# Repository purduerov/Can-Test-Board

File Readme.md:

# Readme for Can-Test-Board

Whenever you make a new part, download the datasheet and save it here _**and**_ with the part in the parts library

Always pull other people's changes before beginning to work
`git pull`

Be sure to push your changes after  working on them. Run:
1. `git add .` to add any files in this directory or a subdirectory
or `git add -u` to add any modified files
2. (Optional) `git clean -nX` to see what ignored files can be removed
	`git clean -fX` removes ignored files (Eagle backups)
3. `git commit -m "helpful commit message"` with a description of the work that you did
4. `git push` to push your work to github

Other helpful commands
* `git status` says information about modified and staged files
* `git log` shows the recent commits of the repository
* `git log filename.extension` show the recent commits for just that file
* `git checkout first-couple-letter-of-commit-id` lets you go back to a previous version
* `git checkout master` brings you back to the latest commit
* `git tag` lists the tags
* `git tag -a orderX -m "the version of the board placed for the X'th order"` tag a specific commit
* `git push --tags` needed to push tags to remote
* `git show orderX` show the commit log for the given tag
* `git checkout orderX` go back and interact with the files at the tagged commit

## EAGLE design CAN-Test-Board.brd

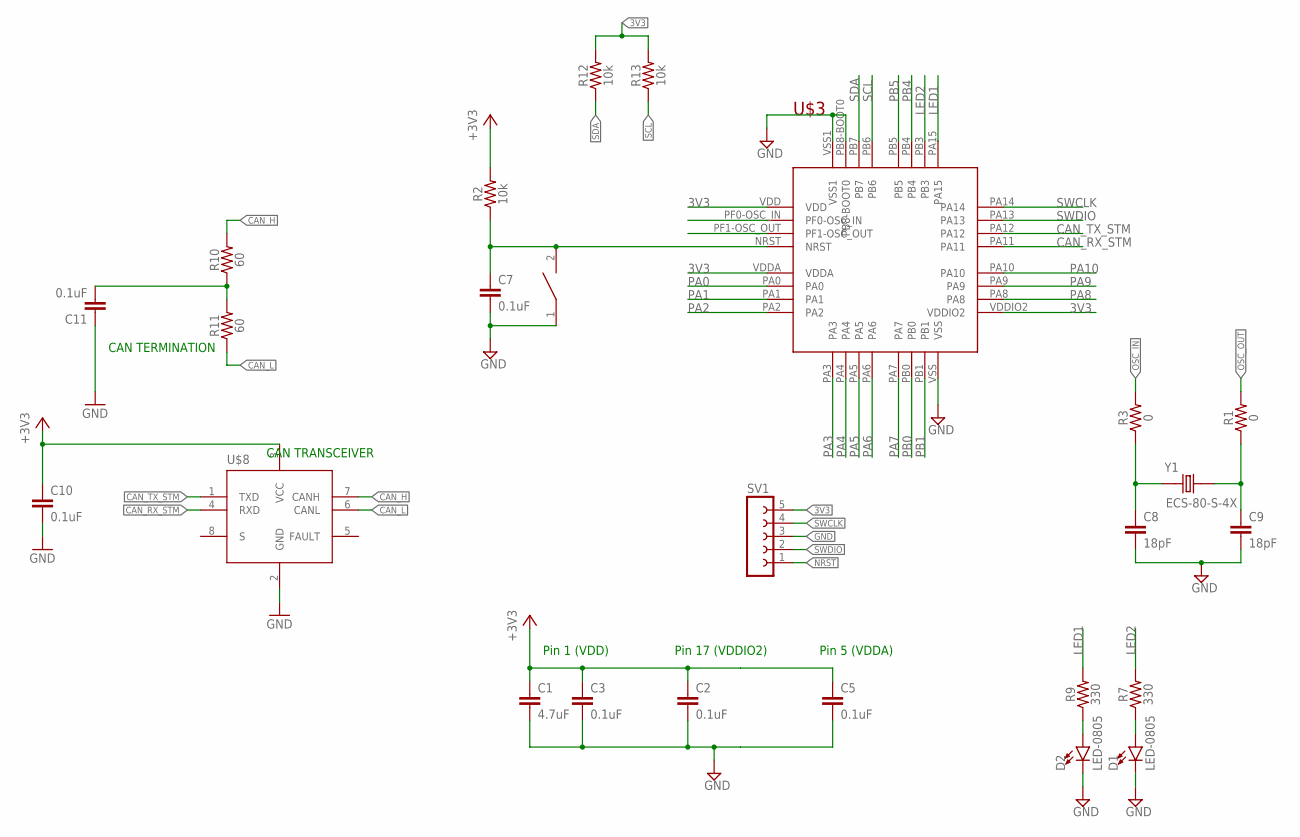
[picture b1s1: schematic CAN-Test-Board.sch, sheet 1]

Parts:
C1: 4.7uF; 0603
C2, C3, C5, C7, C10, C11: 0.1uF; 0603
C8, C9: 18pF; 0603
D1, D2: LED-0805; 0805
R1, R3: 0; 0603
R2, R12, R13: 10k; 0603
R7, R9: 330; 0603
R10, R11: 60; 0603
RESET: DISCRETECOMPONENTS_SWITCH; DISCRETECOMPONENTS_SW_2512
SV1: FE05-1
U$3: STM32F042K6T6
U$8: TCAN337D; SOIC-8
Y1: ECS-80-S-4X; XTAL_ECS-80-S-4X

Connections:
3V3: C1.1, C2.1, C3.1, C5.1, C10.1, R2.2, R12.2, R13.2, SV1.5, U$3.VDD, U$3.VDDA, U$3.VDDIO2, U$8.3 (VCC); also elsewhere on the board
CAN_H: R10.2, U$8.7 (CANH); also elsewhere on the board
CAN_L: R11.1, U$8.6 (CANL); also elsewhere on the board
CAN_RX_STM: U$3.PA11, U$8.4 (RXD)
CAN_TX_STM: U$3.PA12, U$8.1 (TXD)
GND: C1.2, C2.2, C3.2, C5.2, C7.2, C8.2, C9.2, C10.2, C11.1, D1.C, D2.C, RESET.1, SV1.3, U$3.PB8-BOOT0, U$3.VSS, U$3.VSS1, U$8.2 (GND); also elsewhere on the board
LED1: R9.2, U$3.PA15
LED2: R7.2, U$3.PB3; also elsewhere on the board
unnamed: C9.1, R1.1, Y1.2
unnamed: C8.1, R3.1, Y1.1
unnamed: C11.2, R10.1, R11.2
unnamed: D2.A, R9.1
unnamed: D1.A, R7.1
NRST: C7.1, R2.1, RESET.2, SV1.1, U$3.NRST
OSC_IN: R3.2, U$3.PF0-OSC_IN
OSC_OUT: R1.2, U$3.PF1-OSC_OUT
PA0: U$3.PA0; also elsewhere on the board
PA1: U$3.PA1; also elsewhere on the board
PA2: U$3.PA2; also elsewhere on the board
PA3: U$3.PA3; also elsewhere on the board
PA4: U$3.PA4; also elsewhere on the board
PA5: U$3.PA5; also elsewhere on the board
PA6: U$3.PA6; also elsewhere on the board
PA7: U$3.PA7; also elsewhere on the board
PA8: U$3.PA8; also elsewhere on the board
PA9: U$3.PA9; also elsewhere on the board
PA10: U$3.PA10; also elsewhere on the board
PB0: U$3.PB0; also elsewhere on the board
PB1: U$3.PB1; also elsewhere on the board
PB4: U$3.PB4; also elsewhere on the board
PB5: U$3.PB5; also elsewhere on the board
SCL: R13.1, U$3.PB6; also elsewhere on the board
SDA: R12.1, U$3.PB7; also elsewhere on the board
SWCLK: SV1.4, U$3.PA14
SWDIO: SV1.2, U$3.PA13

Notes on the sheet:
CAN TRANSCEIVER
CAN TERMINATION
Pin 1 (VDD)
Pin 17 (VDDIO2)
Pin 5 (VDDA)

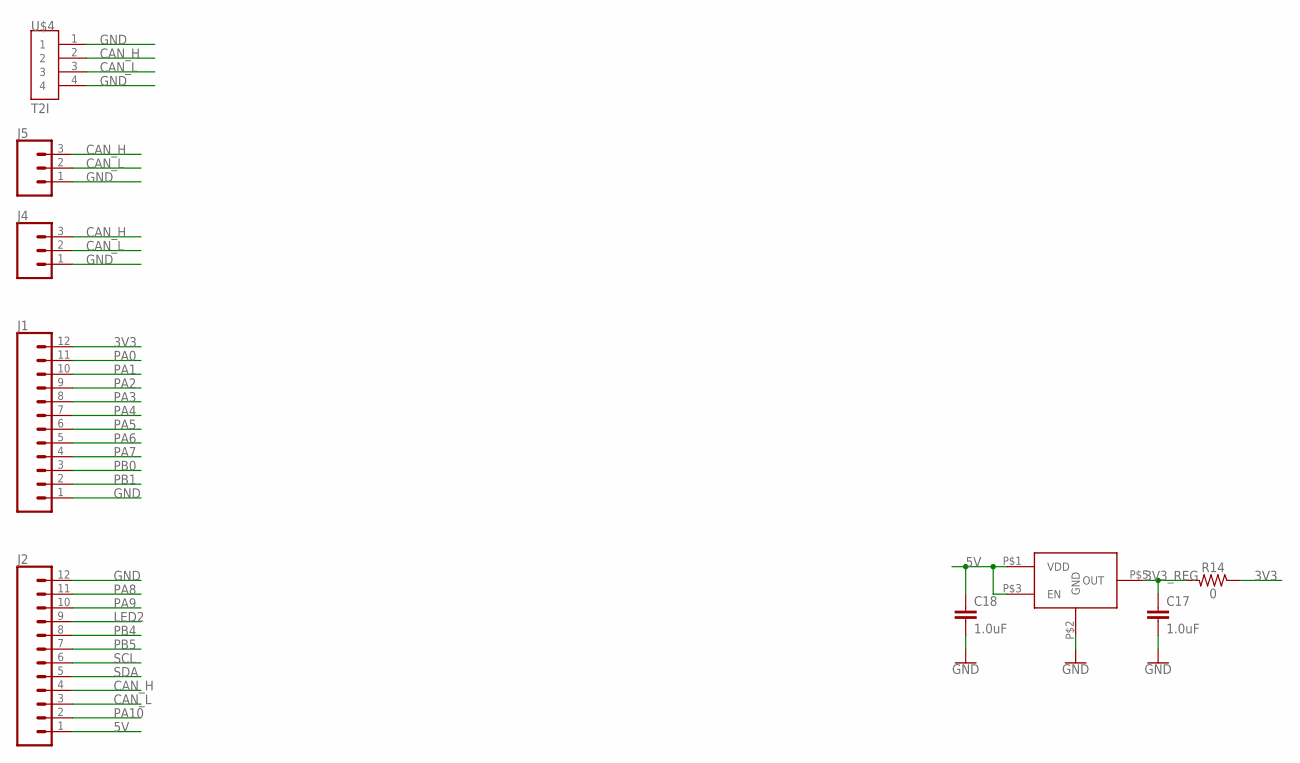
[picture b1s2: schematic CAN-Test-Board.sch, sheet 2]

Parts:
C17, C18: 1.0uF; 0603
J1, J2: CONN_12; 1X12
J4, J5: CONN_03; 1X03
R14: 0; 0603
U$4: T2I
U$5: NCP114; TSOP-5

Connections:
3V3: J1.12, R14.1; also elsewhere on the board
3V3_REG: C17.1, R14.2, U$5.P$5 (OUT)
5V: C18.1, J2.1, U$5.P$1 (VDD), U$5.P$3 (EN); also elsewhere on the board
CAN_H: J2.4, J4.3, J5.3, U$4.2; also elsewhere on the board
CAN_L: J2.3, J4.2, J5.2, U$4.3; also elsewhere on the board
GND: C17.2, C18.2, J1.1, J2.12, J4.1, J5.1, U$4.1, U$4.4, U$5.P$2 (GND); also elsewhere on the board
LED2: J2.9; also elsewhere on the board
PA0: J1.11; also elsewhere on the board
PA1: J1.10; also elsewhere on the board
PA2: J1.9; also elsewhere on the board
PA3: J1.8; also elsewhere on the board
PA4: J1.7; also elsewhere on the board
PA5: J1.6; also elsewhere on the board
PA6: J1.5; also elsewhere on the board
PA7: J1.4; also elsewhere on the board
PA8: J2.11; also elsewhere on the board
PA9: J2.10; also elsewhere on the board
PA10: J2.2; also elsewhere on the board
PB0: J1.3; also elsewhere on the board
PB1: J1.2; also elsewhere on the board
PB4: J2.8; also elsewhere on the board
PB5: J2.7; also elsewhere on the board
SCL: J2.6; also elsewhere on the board
SDA: J2.5; also elsewhere on the board

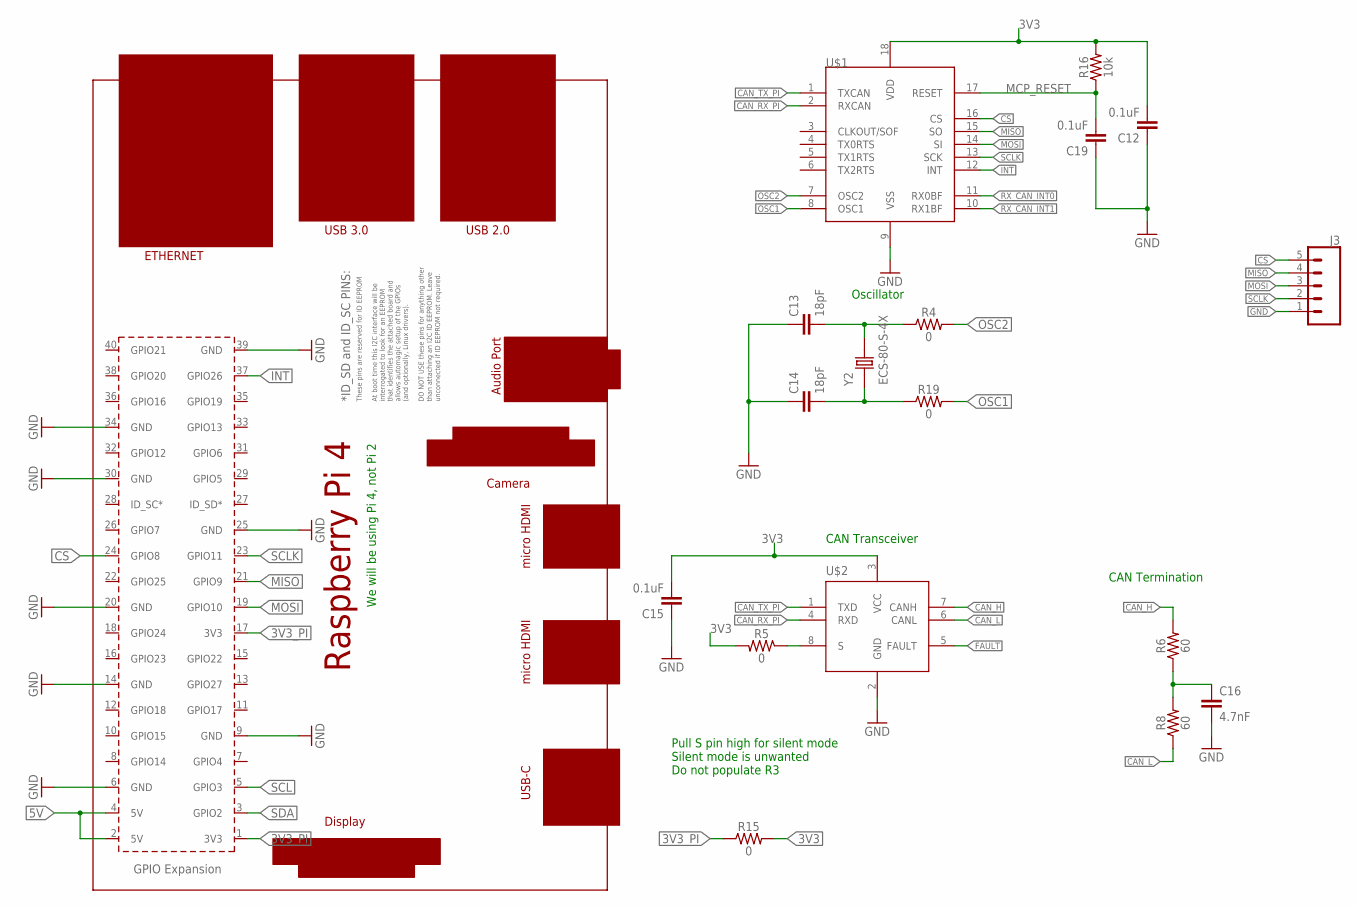
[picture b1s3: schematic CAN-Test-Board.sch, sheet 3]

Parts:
C12, C15, C19: 0.1uF; 0603
C13, C14: 18pF; 0603
C16: 4.7nF; 0603
J3: CONN_05; 1X05
PCB1: RPI4
R4, R5, R15, R19: 0; 0603
R6, R8: 60; 0603
R16: 10k; 0603
U$1: MCP2515; SOIC-18
U$2: TCAN337D; SOIC-8
Y2: ECS-80-S-4X; XTAL_ECS-80-S-4X

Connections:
3V3: C12.2, C15.2, R5.2, R15.2, R16.2, U$1.18 (VDD), U$2.3 (VCC); also elsewhere on the board
3V3_PI: PCB1.1 (3V3), PCB1.17 (3V3), R15.1
5V: PCB1.2 (5V), PCB1.4 (5V); also elsewhere on the board
CAN_H: R6.2, U$2.7 (CANH); also elsewhere on the board
CAN_L: R8.1, U$2.6 (CANL); also elsewhere on the board
CAN_RX_PI: U$1.2 (RXCAN), U$2.4 (RXD)
CAN_TX_PI: U$1.1 (TXCAN), U$2.1 (TXD)
CS: J3.5, PCB1.24 (GPIO8), U$1.16 (CS)
FAULT: U$2.5 (FAULT)
GND: C12.1, C13.1, C14.1, C15.1, C16.2, C19.1, J3.1, PCB1.6 (GND), PCB1.9 (GND), PCB1.14 (GND), PCB1.20 (GND), PCB1.25 (GND), PCB1.30 (GND), PCB1.34 (GND), PCB1.39 (GND), U$1.9 (VSS), U$2.2 (GND); also elsewhere on the board
INT: PCB1.37 (GPIO26), U$1.12 (INT)
MCP_RESET: C19.2, R16.1, U$1.17 (RESET)
MISO: J3.4, PCB1.21 (GPIO9), U$1.15 (SO)
MOSI: J3.3, PCB1.19 (GPIO10), U$1.14 (SI)
unnamed: C16.1, R6.1, R8.2
OSC1: R19.2, U$1.8 (OSC1)
OSC2: R4.2, U$1.7 (OSC2)
OSC_1_MID: C14.2, R19.1, Y2.1
OSC_2_MID: C13.2, R4.1, Y2.2
RX_CAN_INT0: U$1.11 (RX0BF)
RX_CAN_INT1: U$1.10 (RX1BF)
SCL: PCB1.5 (GPIO3); also elsewhere on the board
SCLK: J3.2, PCB1.23 (GPIO11), U$1.13 (SCK)
SDA: PCB1.3 (GPIO2); also elsewhere on the board
SILENT_PI: R5.1, U$2.8 (S)

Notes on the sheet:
Oscillator
CAN Transceiver
CAN Termination
Pull S pin high for silent mode Silent mode is unwanted Do not populate R3
We will be using Pi 4, not Pi 2

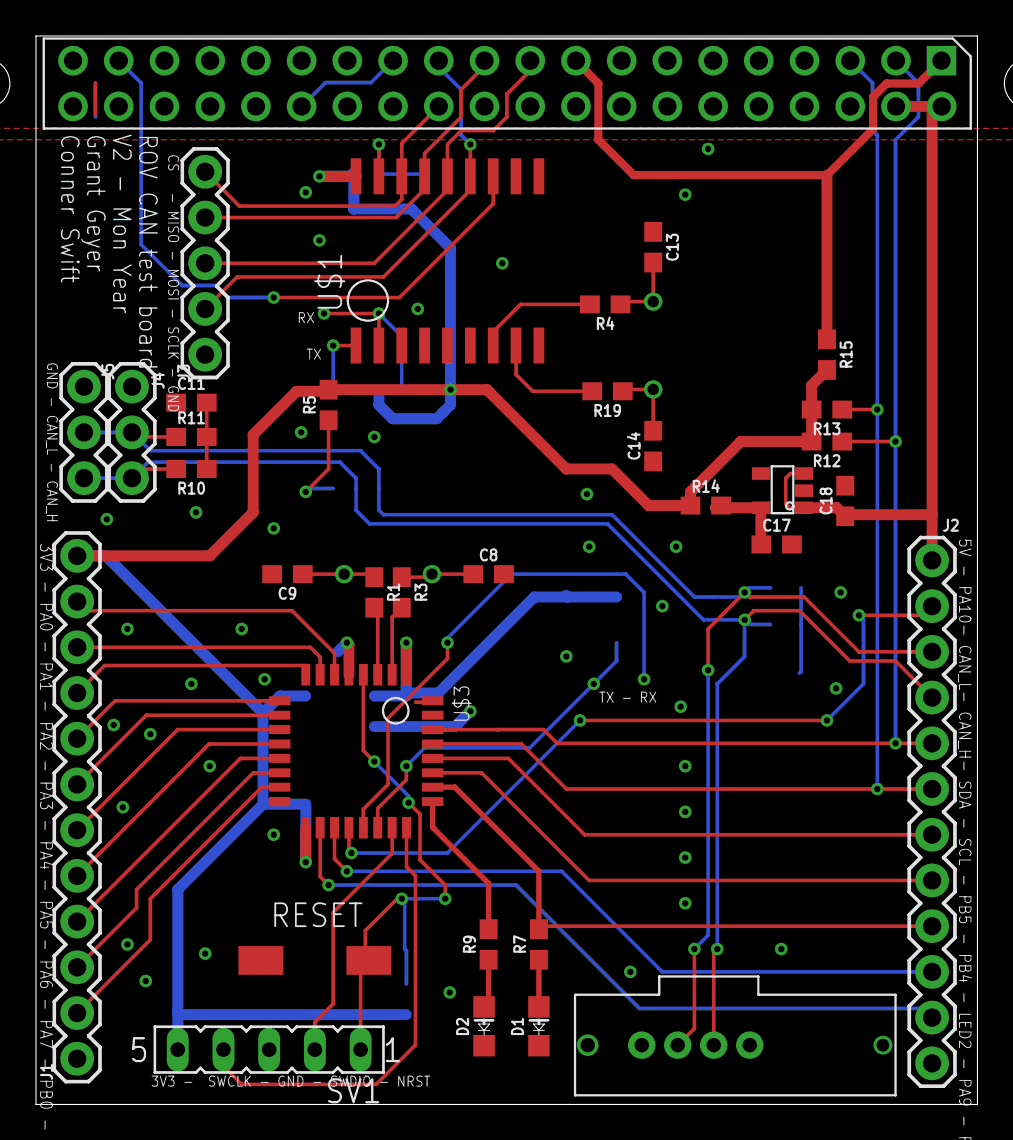
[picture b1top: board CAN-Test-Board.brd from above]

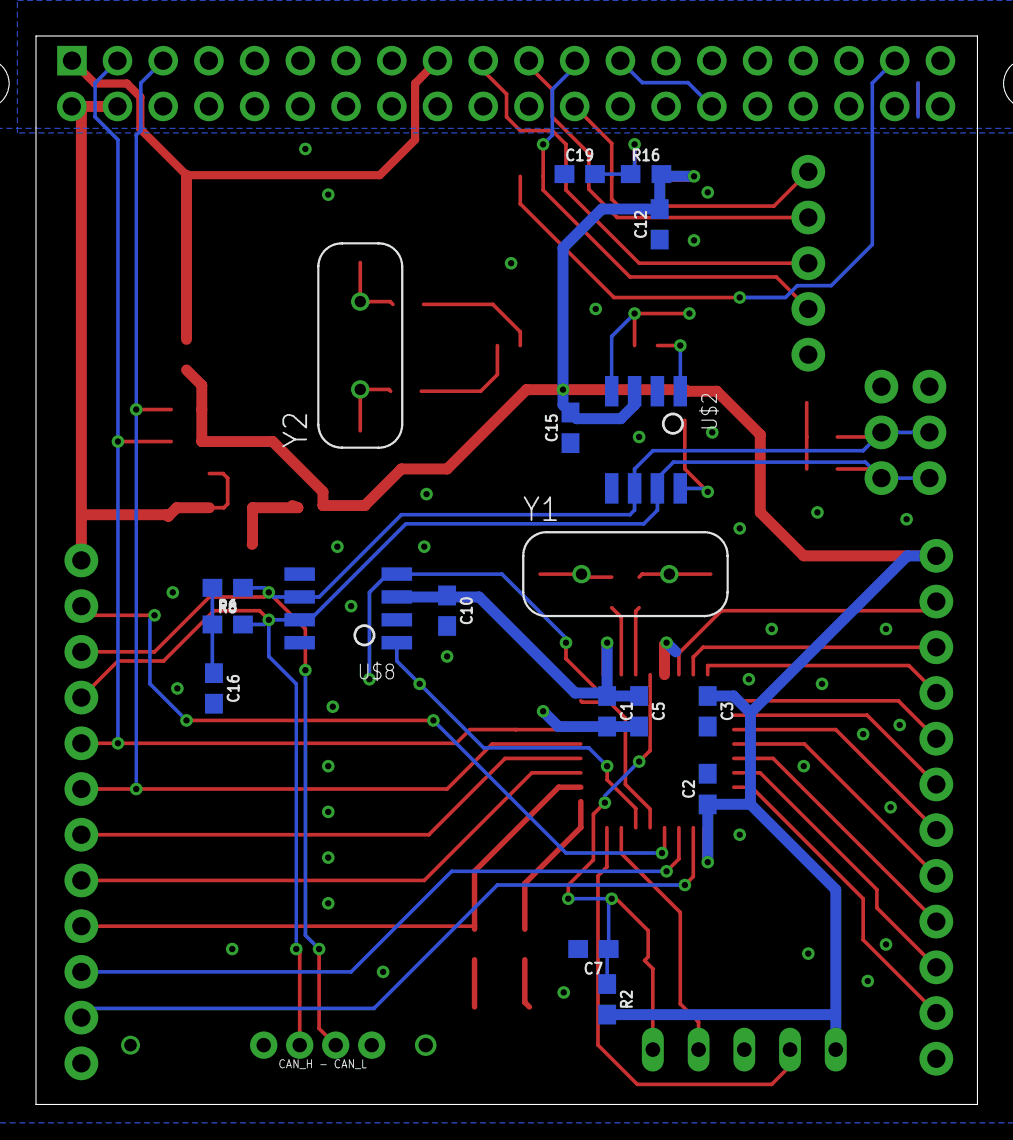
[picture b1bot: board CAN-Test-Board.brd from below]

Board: 2 copper layers, 52.3 x 59.4 mm, 52 parts (18 on the bottom side), 52 nets.

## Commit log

2020-09-05 first design
2020-09-08 smaller and extra CAN breakouts
2020-09-09 labels and 3v3 power options
2020-09-09 datasheets
2020-09-11 smaller
2020-09-12 added samtec t2i
2020-09-13 little better CAN trace routing around PI transceiver
2020-09-23 CAM for order and parts list
2020-09-23 changed schematic to pages
2020-09-23 couple part values
2020-10-13 couple changes for a possible rev 2 (led sizes, button footprint)
2021-04-03 Shorted Reset to 3V3 instead of leaving it floating
2021-05-20 Add missing interrupt connection
2021-08-11 Update parts and values. Fix missing connection?

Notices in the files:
parts and their libraries:
SparkFun-Capacitors: Licensing: Creative Commons ShareAlike 4.0 International - https://creativecommons.org/licenses/by-sa/4.0
